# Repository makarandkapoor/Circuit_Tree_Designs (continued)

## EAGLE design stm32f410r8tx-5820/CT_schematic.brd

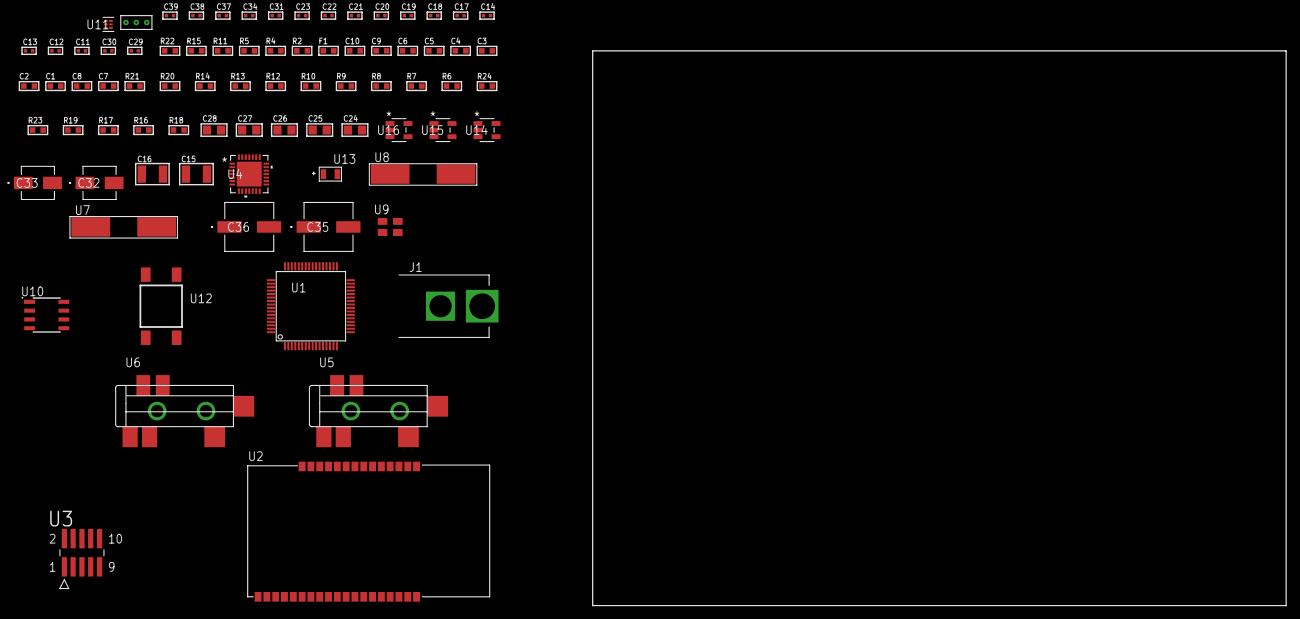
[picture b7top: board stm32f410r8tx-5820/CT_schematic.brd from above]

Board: 2 copper layers, 100.0 x 80.0 mm, 80 parts (0 on the bottom side), 36 nets, no tracks yet.

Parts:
C1, C10: 1e-06; C0603
C2, C3, C4, C5, C6: 1e-07; C0603
C7: 4.7e-06; C0603
C8: 2.2e-06; C0603
C9: 1e-08; C0603
C11, C12: 1e-11; C0402
C13, C14, C19, C20, C21, C22, C23, C34: 1e-07; C0402
C15, C16: 2.2e-05; C1210
C17, C18: 1e-09; C0402
C24, C25, C26, C27, C28: 1e-05; C0805
C29, C30: 2.2e-11; C0402
C31, C37, C38, C39: 1e-08; C0402
C32: 1e-06; EXV-9B
C33: 2.2e-06; EXV-9B
C35, C36: 0.0001; EXV-9H
F1: 240.0; L0603
J1: PJ-037B; PJ-037B_PACKAGE
R2: 1000.0; R0603
R4, R5: 4700.0; R0603
R6, R7, R8, R9, R10, R20, R21: 10000.0; R0603
R11: 5.0; R0603
R12, R13, R14: 47000.0; R0603
R15: 680.0; R0603
R16, R17, R19: 100000.0; R0603
R18: 164658.62; R0603
R22: 9100.0; R0603
R23: 680000.0; R0603
R24: 120000.0; R0603
U1: STM32F410R8T6; LQFP64
U2: ETRX3587
U3: FTSH-105-01-L-DV-K; SAMTEC_FTSH-105-01-L-DV-K
U4: WM8731CLSEFL; QFN-28
U5, U6: SJ-43515TS-SMT-TR
U7: ABLS-25.000MHZ-B2F-T
U8: ABLS-12.288MHZ-B4-T
U9: ASEK-32.768KHz-ECST; ASEK
U10: LP2954AIMX/NOPB; LP2954
U11: TPS3895ADRYR; SON-6
U12: 4-1437565-2; SW_4-1437565-2
U13: Q65110A2395; LGM67K-G1J2-24-Z
U14, U15, U16: nc7sz125m5x; NC7SZ125M5X
U17: Dummy; DUMMY_PACKAGE_165

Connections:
CLK_CRYSTAL_U1_5: C11.1, U1.5, U7.1
CLK_CRYSTAL_U1_6: C12.1, U1.6, U7.2
CLK_CRYSTAL_U4_1: C29.1, U4.1, U8.1
CLK_CRYSTAL_U4_2: C30.1, U4.2, U8.2
CLK_U1_3: U1.3, U9.3
GND: C1.2, C2.2, C3.2, C4.2, C5.2, C6.2, C7.2, C8.2, C9.2, C10.2, C11.2, C12.2, C13.2, C14.2, C18.2, C19.2, C20.2, C21.2, C22.2, C23.2, C24.2, C25.2, C26.2, C27.2, C28.2, C29.2, C30.2, C31.2, C32.2, C33.2, C34.2, C35.2, C36.2, C37.2, C38.2, C39.2, J1.2, R2.2, R6.2, R7.2, R11.2, R12.2, R13.2, R14.2, R19.2, R22.2, R24.2, U1.12, U1.18, U1.31, U1.47, U1.63, U2.1, U2.13, U2.19, U2.20, U2.31, U2.33, U3.3, U3.5, U4.4, U4.15, U4.19, U4.25, U4.26, U4.29, U5.1, U6.1, U9.2, U10.4, U11.2, U13.C, U14.2, U14.3, U15.1, U15.3, U16.1, U16.3, U17.1
NET_U1_7: R5.1, U1.7, U16.4
NET_U1_13: C9.1, C10.1, F1.1, U1.13
NET_U1_30: C8.1, U1.30
NET_U1_60: R6.1, U1.60
NET_U1_62: U12.3, U12.4
NET_U2_7: R4.1, U2.7, U15.4
NET_U2_21: R7.1, U2.21
NET_U3_9: R11.1, U3.9
NET_U4_20: C23.1, C28.1, U4.20
NET_U5_2: C16.1, R13.1, U5.2
NET_U5_5: C15.1, R12.1, U5.5
NET_U6_5: C17.1, C18.1, R14.1, R15.1, U6.5
NET_U10_3: R17.1, U10.3
NET_U10_5: R16.1, U10.5
NET_U10_7: R18.2, R19.1, U10.7
NET_U11_1: R21.1, R22.1, U11.1
NET_U11_3: R23.2, R24.1, U11.3
NET_U11_4: R20.1, U11.4, U14.4, U15.2, U16.2
NET_U12_1: R2.1, U12.1, U12.2
PROC_ADC1_IN1: U1.15, U17.3
PROC_ADC1_IN2: U1.16, U17.2
PROC_I2S1_CK: U1.21, U4.7
PROC_I2S1_SD: U1.23, U4.8
PROC_I2S1_WS: U1.20, U4.9, U4.11
PROC_SYS_JTCK_SWCLK: R9.1, U1.49, U3.4
PROC_SYS_JTDO_SWO: U1.55, U3.6
PROC_SYS_JTMS_SWDIO: R10.1, U1.46, U3.2
RST_OUT_U3_JTAG_RST_B: R8.1, U3.10, U14.1
VCC_S1_11V6: C32.1, C35.1, C36.1, J1.1, R17.2, U10.8
VCC_TIER1_3V3: C1.1, C2.1, C3.1, C4.1, C5.1, C6.1, C7.1, C13.1, C14.1, C19.1, C20.1, C21.1, C22.1, C24.1, C25.1, C26.1, C27.1, C31.1, C33.1, C34.1, C37.1, C38.1, C39.1, F1.2, R4.2, R5.2, R8.2, R9.2, R10.2, R16.2, R18.1, R20.2, R21.2, R23.1, U1.1, U1.19, U1.32, U1.48, U1.64, U2.32, U3.1, U4.3, U4.5, U4.12, U4.18, U9.4, U10.1, U11.6, U14.5, U15.5, U16.5

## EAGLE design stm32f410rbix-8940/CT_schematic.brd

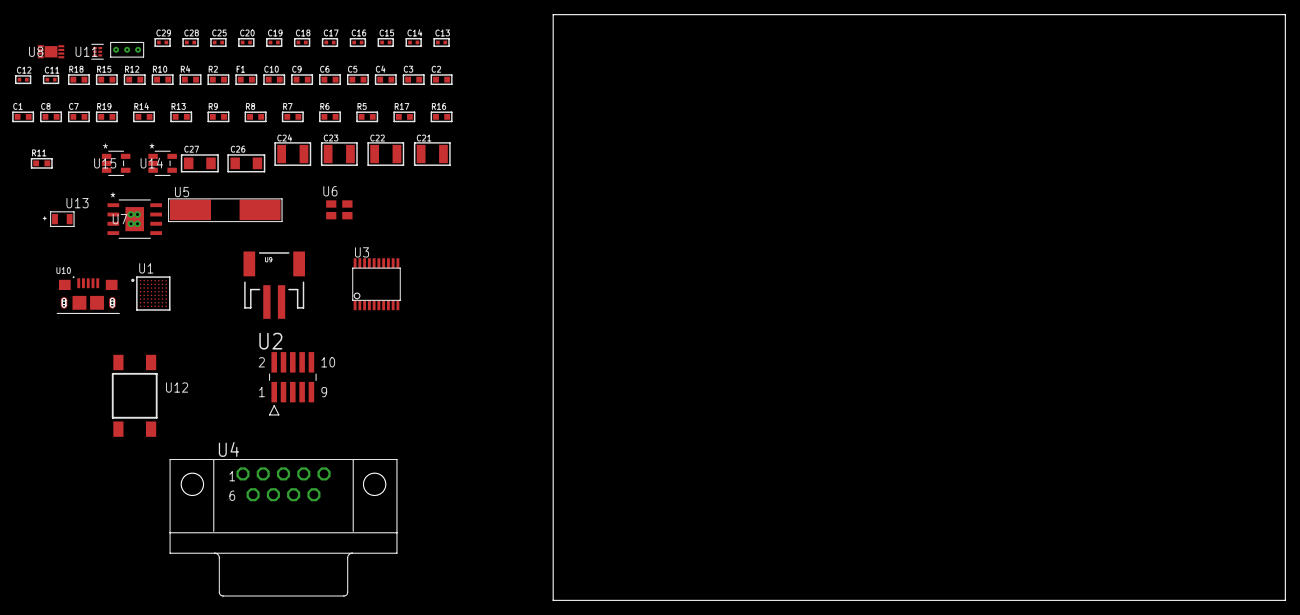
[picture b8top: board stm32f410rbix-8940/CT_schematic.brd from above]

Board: 2 copper layers, 167.1 x 80.0 mm, 63 parts (0 on the bottom side), 41 nets, no tracks yet.

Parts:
C1, C10: 1e-06; C0603
C2, C3, C4, C5, C6: 1e-07; C0603
C7: 4.7e-06; C0603
C8: 2.2e-06; C0603
C9: 1e-08; C0603
C11, C12: 1e-11; C0402
C13, C14, C15, C16, C17, C18, C19, C25: 1e-07; C0402
C20, C28, C29: 1e-08; C0402
C21, C22, C23, C24: 1e-05; C1210
C26, C27: 1e-05; C1206
F1: 240.0; L0603
R2: 1000.0; R0603
R4: 4700.0; R0603
R5, R6, R7, R8, R9, R13, R14, R19: 10000.0; R0603
R10: 5.0; R0603
R11: 4031.5447154472; R0603
R12: 2200.0; R0603
R15: 9100.0; R0603
R16: 680000.0; R0603
R17: 120000.0; R0603
R18: 2000.0; R0603
U1: STM32F410RBI6; UFBGA64
U2: FTSH-105-01-L-DV-K; SAMTEC_FTSH-105-01-L-DV-K
U3: SP3203ECY-L/TR; TSSOP20-I
U4: 182-009-113R531; 182-009-MALE
U5: ABLS-25.000MHZ-B2F-T
U6: ASEK-32.768KHz-ECST; ASEK
U7: MIC5234YME; SOIC-8_EP
U8: MCP73831T-2ACI/MC; DFN8_2X3MC
U9: S2B-PH-SM4-TB(LF)(SN); JST-2-SMD
U10: 10118193-0001LF; FCI_10118193-0001LF
U11: TPS3895ADRYR; SON-6
U12: 4-1437565-2; SW_4-1437565-2
U13: Q65110A2395; LGM67K-G1J2-24-Z
U14, U15: nc7sz125m5x; NC7SZ125M5X
U16: Dummy; DUMMY_PACKAGE_134

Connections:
CLK_CRYSTAL_U1_C1: C11.1, U1.C1, U5.1
CLK_CRYSTAL_U1_D1: C12.1, U1.D1, U5.2
CLK_U1_A1: U1.A1, U6.3
GND: C1.2, C2.2, C3.2, C4.2, C5.2, C6.2, C7.2, C8.2, C9.2, C10.2, C11.2, C12.2, C13.2, C14.2, C15.2, C18.2, C19.2, C20.2, C21.2, C22.2, C23.2, C24.2, C25.2, C26.2, C27.2, C28.2, C29.2, R2.2, R5.2, R10.2, R12.2, R15.2, R17.2, R18.2, U1.C2, U1.D5, U1.D6, U1.F1, U2.3, U2.5, U3.18, U4.5, U6.2, U7.7, U7.EPAD, U8.6, U8.9, U9.2, U10.5, U10.6, U10.7, U10.8, U10.9, U11.2, U13.C, U14.2, U14.3, U15.1, U15.3, U16.1
INPUT_USBPOWER_5V: C26.1, R19.2, U8.1, U8.2, U10.1
NET_U1_A4: R5.1, U1.A4
NET_U1_C3: R6.1, U1.C3
NET_U1_E1: R4.1, U1.E1, U15.4
NET_U1_H1: C9.1, C10.1, F1.1, U1.G1, U1.H1
NET_U1_H7: C8.1, U1.H7
NET_U1_H8: U12.3, U12.4
NET_U2_9: R10.1, U2.9
NET_U3_1: C16.1, U3.1
NET_U3_2: C18.1, U3.2
NET_U3_3: C16.2, U3.3
NET_U3_4: C17.1, U3.4
NET_U3_5: C17.2, U3.5
NET_U3_6: C19.1, U3.6
NET_U4_2: U3.14, U4.2
NET_U4_3: U3.17, U4.3
NET_U4_7: U3.13, U4.7
NET_U4_8: U3.16, U4.8
NET_U7_4: R11.2, R12.1, U7.4
NET_U8_5: R19.1, U8.5
NET_U8_8: R18.1, U8.8
NET_U11_1: R14.1, R15.1, U11.1
NET_U11_3: R16.2, R17.1, U11.3
NET_U11_4: R13.1, U11.4, U14.4, U15.2
NET_U12_1: R2.1, U12.1, U12.2
PROC_ADC1_IN1: U1.H2, U16.3
PROC_ADC1_IN2: U1.F3, U16.2
PROC_SYS_JTCK_SWCLK: R8.1, U1.B7, U2.4
PROC_SYS_JTDO_SWO: U1.A5, U2.6
PROC_SYS_JTMS_SWDIO: R9.1, U1.C7, U2.2
PROC_USART1_CTS: U1.D7, U3.8
PROC_USART1_RTS: U1.A8, U3.10
PROC_USART1_RX: U1.B4, U3.11
PROC_USART1_TX: U1.A7, U3.7
RST_OUT_U2_JTAG_RST_B: R7.1, U2.10, U14.1
VCC_S1_3V7: C21.1, C22.1, C27.1, U7.5, U7.8, U8.3, U8.4, U9.1
VCC_TIER1_3V3: C1.1, C2.1, C3.1, C4.1, C5.1, C6.1, C7.1, C13.1, C14.1, C15.1, C20.1, C23.1, C24.1, C25.1, C28.1, C29.1, F1.2, R4.2, R6.2, R7.2, R8.2, R9.2, R11.1, R13.2, R14.2, R16.1, U1.A2, U1.D2, U1.E4, U1.E5, U2.1, U3.12, U3.19, U6.4, U7.1, U11.6, U14.5, U15.5
